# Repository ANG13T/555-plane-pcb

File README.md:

# 555 Airplane PCB with Astable Dual LED Flashing ✈️
A simple airplane PCB to teach the principles of the 555 timer IC and astable mode using blinking LEDs.

## Schematic

## PCB Design

## Bill of Materials
| Component                   | Link                                                                                                      |
|-----------------------------|-----------------------------------------------------------------------------------------------------------|
| 1x 3mm Red LED             | [Amazon Link](https://www.amazon.com/Diode-Lights-120Pcs-Emitting-Assorted/dp/B0BY28JTFC/ref=sr_1_4?sr=8-4) |
| 1x 3mm Green LED           | [Amazon Link](https://www.amazon.com/Diode-Lights-120Pcs-Emitting-Assorted/dp/B0BY2CZN7M/ref=sr_1_2?sr=8-2) |
| 1x 3mm White LED           | [Amazon Link](https://www.amazon.com/Diode-Lights-120Pcs-Emitting-Assorted/dp/B0BY2DDW65/ref=sr_1_5?sr=8-5) |
| NE555 IC                    | [Amazon Link](https://www.amazon.com/MCIGICM-ne555-Timer-Pulse-Generator/dp/B077BRB6W6/ref=sr_1_2?sr=8-2) |
| 10uF - 50V Electrolytic Capacitor| [Amazon Link](https://www.amazon.com/ALLECIN-Electrolytic-Capacitor-0-2x0-43in-Capacitors/dp/B0CMQ958P5/ref=sr_1_3?crid=2ICLQ9FUBW19B&dib=eyJ2IjoiMSJ9.C47EZG-dnalYqTdKMkTS05zReWTQ19mcpxs4N_frXipdp5XSQiWz4c7zb-2pxkbMmGGnHyfwyHGS_GD-nd8Jmuj44WOG_C18SbRbJntl3-i8rgk9XD6lwg15ccN5xahj6pxgjSOev29LfAQDMl4G1u9uS8hSIrsBCetQIRGDxxxoDjcCTdLhqSaNBkuguRSMJs1OhP_L-0RoonNdno3RzyHwfENFL2Gq4jAt6KebyP10fBdW3NigkikWa2jYVdLuwDC1kD5hmHFlR0ozY7yCY2_-evbQXFzFGJl-ohzh3Mw._F0t1BZz3gJ8Bi-dTDPeWECma9IJrG3_ymgolVShfdU&dib_tag=se&keywords=ALLECIN+10uF+50V+5x11mm+Electrolytic+Capacitor+10+UF+MFD+50+Volt+0.2x0.43in+Aluminum+Capacitors+%28Pack+of+15%29&qid=1727495312&s=industrial&sprefix=allecin+10uf+50v+5x11mm+electrolytic+capacitor+10+uf+mfd+50+volt+0.2x0.43in+aluminum+capacitors+pack+of+15+%2Cindustrial%2C614&sr=1-3) |
| 3V Coin Cell Battery        | [Amazon Link](https://www.amazon.com/LiCB-CR2032-Lithium-Battery-10-Pack/dp/B071D4DKTZ/ref=sr_1_8?sr=8-8) |
| 3V Coin Cell Battery Holder | [Amazon Link](https://www.amazon.com/bnafes-Surface-CR2032-Button-Battery/dp/B09KG8S6Z9/ref=sr_1_3?sr=8-3) |
| 1.2k ohm Axial Resistor    | [Amazon Link](https://www.amazon.com/Resistor-Tolerance-Resistors-Limiting-Certificated/dp/B08QRLJJMC/ref=sr_1_1?dib=eyJ2IjoiMSJ9.bFnVsUm-rVIZ6nX8IE_TEPs7SgKgCY3qj1LEilxAHpuvGoYnb3mmiQbKKKpo_tM6u-t2sj83XdvzmXBt9RKYuscte5cM64rO5gwJF7Q2mJHEqQ6HsQSrPICmN9_nm_wJEFFB8QsNW6jEbVCV2X12iC20LLi6wLUwBakHlDmNA9R1VerKR5a2s5Ljt-hzVRfmMenS-k2R81ucrrkHRmhCZkBb2QShM-brWdWwz93MzvQ.LCsJyJAFStVPh2yPoYC7kh_r7XQRArlWfB6xSpTg1yc&dib_tag=se&keywords=1.2k+ohm+Axial+Resistor&qid=1726619978&sr=8-1) |
| 90 ohm Axial Resistor      | [Amazon Link](https://www.amazon.com/Resistor-Tolerance-Resistors-Limiting-Certificated/dp/B08QRCQY4J/ref=sr_1_1?crid=F2035RURHFBE&dib=eyJ2IjoiMSJ9.x79ivvPhUMsOgn0mwYi9HUloh9rnRkPpkXcuSqcw5OXEl9Cs1SuK7oR7BfTgjhcwOo_rqmqnKAM40pgPe2HuJyJLvH-tKOiYtoQv4_Z_gx0eyhZ2A_wuGBNZC3UL7YncR_JdDpczxGDcS4udbnNEJzen4JAIEpgiWtH1PSp4bgNQaFhoFz2KVE_hxS4hzb3GkhP3tD9eyJu9U71x6Od3G-ec5ASPbc3hb2fvMvKYevM.9YJKewUHyJnDPIFXBN1C6Bp7SCnlo2DcytGkNcYiPLE&dib_tag=se&keywords=90+ohm+Axial+Resistor&qid=1726619999&sprefix=1.2k+ohm+axial+resistor%2Caps%2C245&sr=8-1) |
| SPDT Slide Switch          | [Amazon Link](https://www.amazon.com/HiLetgo-SS-12D00-Toggle-Switch-Vertical/dp/B07RTJDW27/ref=sr_1_2?sr=8-2) |
| 100k Potentiometer          | [Amazon Link](https://www.amazon.com/Sscon-Breadboard-Potentiometer-Arduino-3386MP-104/dp/B07QZ67C2K/ref=sr_1_7?crid=1ZQ1S7PVZS21Z&dib=eyJ2IjoiMSJ9.ALke2vkdw7lw76jKYVkSCsz7yyM2giK0dFq_aH_VpgXj6_QP1JfsWtv0vz2UfV4qxAuq7Htfpj3h7HFThshZVkfJSjn-1LK_C05GDaOsFXdy7CHmUE8g6ZAux-A8Mg8fl7HIi1_cJc2JLeZ1H9VO_XPKU_RMg4UzblocHcNDzP0vG59jG24hv_xCvfZdxmIBon_iU5moHPPxIBydwMKM1kP2T3MDoluO-GZkw-gWJkg.H77FQo1L84C_nGlk5uuYeE7-Us3chvHOX5xWOAhK78I&dib_tag=se&keywords=100k+trim+Potentiometer&qid=1726620068&sprefix=100k+trim+potentiometer%2Caps%2C157&sr=8-7) |

## Design Analysis: Pulse Time and Duty Cycle Determination

The duty cycle of a circuit is ratio of the time the signal is active (high) to the total period of the signal. 
We want the duty cycle of this circuit to be close to 50% in order to get a congruent off/on blinking pattern form the airplane LEDs.

*R1:R2 ratio predominately is what sets the duty cycle for the circuit*

#### Output High Time Interval of Pulse

$$
t_h = ln(2) * (R_1 + R_2) * C
$$

#### Output Low Time Interval of Pulse

$$
t_l = ln(2) * R_2 * C
$$

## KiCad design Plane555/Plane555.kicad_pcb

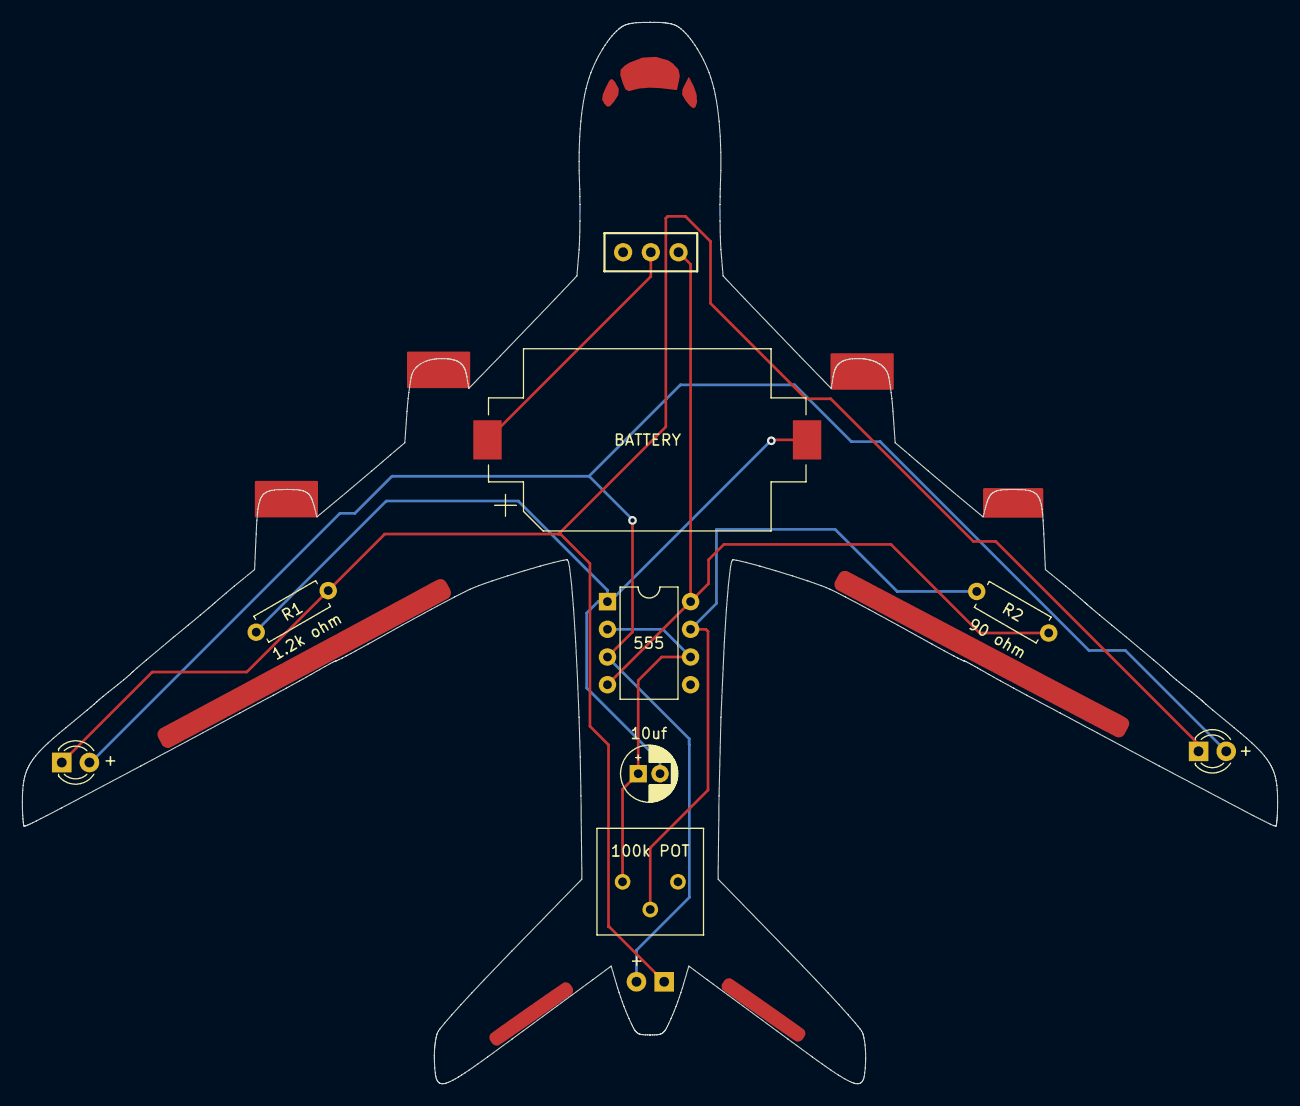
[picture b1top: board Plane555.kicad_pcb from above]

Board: 2 copper layers, 115.1 x 97.3 mm, 10 parts (1 on the bottom side), 7 nets.

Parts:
100k POT: POT; Potentiometer_Bourns_3386P_Vertical
555: LM555xM; DIP-8_W7.62mm
BATTERY: BATTERY; BatteryHolder_Keystone_1060_1x2032
C1: 10uf; CP_Radial_D5.0mm_P2.00mm
D1: LED; LED_D3.0mm_Horizontal_O1.27mm_Z2.0mm
D2, D3: LED; LED_D3.0mm
R1: 1.2k ohm; R_Axial_DIN0207_L6.3mm_D2.5mm_P7.62mm_Horizontal
R2: 90 ohm; R_Axial_DIN0207_L6.3mm_D2.5mm_P7.62mm_Horizontal
SW1: SW_SPDT; Schiebeschalter_SS-12D00

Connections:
+3V0: 555.4 (R), 555.8 (VCC), R2.2, SW1.3 (C)
GNDREF: 555.1 (GND), BATTERY.2 (-), C1.2, R1.1
unnamed: BATTERY.1 (+), SW1.2 (B)
unnamed: 555.3 (Q), D1.2 (A), D2.2 (A), D3.2 (A)
unnamed: D1.1 (K), D2.1 (K), D3.1 (K), R1.2
unnamed: 100k POT.2, 555.7 (DIS), R2.1
unnamed: 100k POT.1, 555.2 (TR), 555.6 (THR), C1.1

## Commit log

2024-05-03 feat: init commit
2024-08-02 feat: update board trace and R values
2024-09-03 feat: update R values
2024-09-03 feat: update silk screen
2024-09-18 feat: init new files
2024-09-18 feat: update BOM
